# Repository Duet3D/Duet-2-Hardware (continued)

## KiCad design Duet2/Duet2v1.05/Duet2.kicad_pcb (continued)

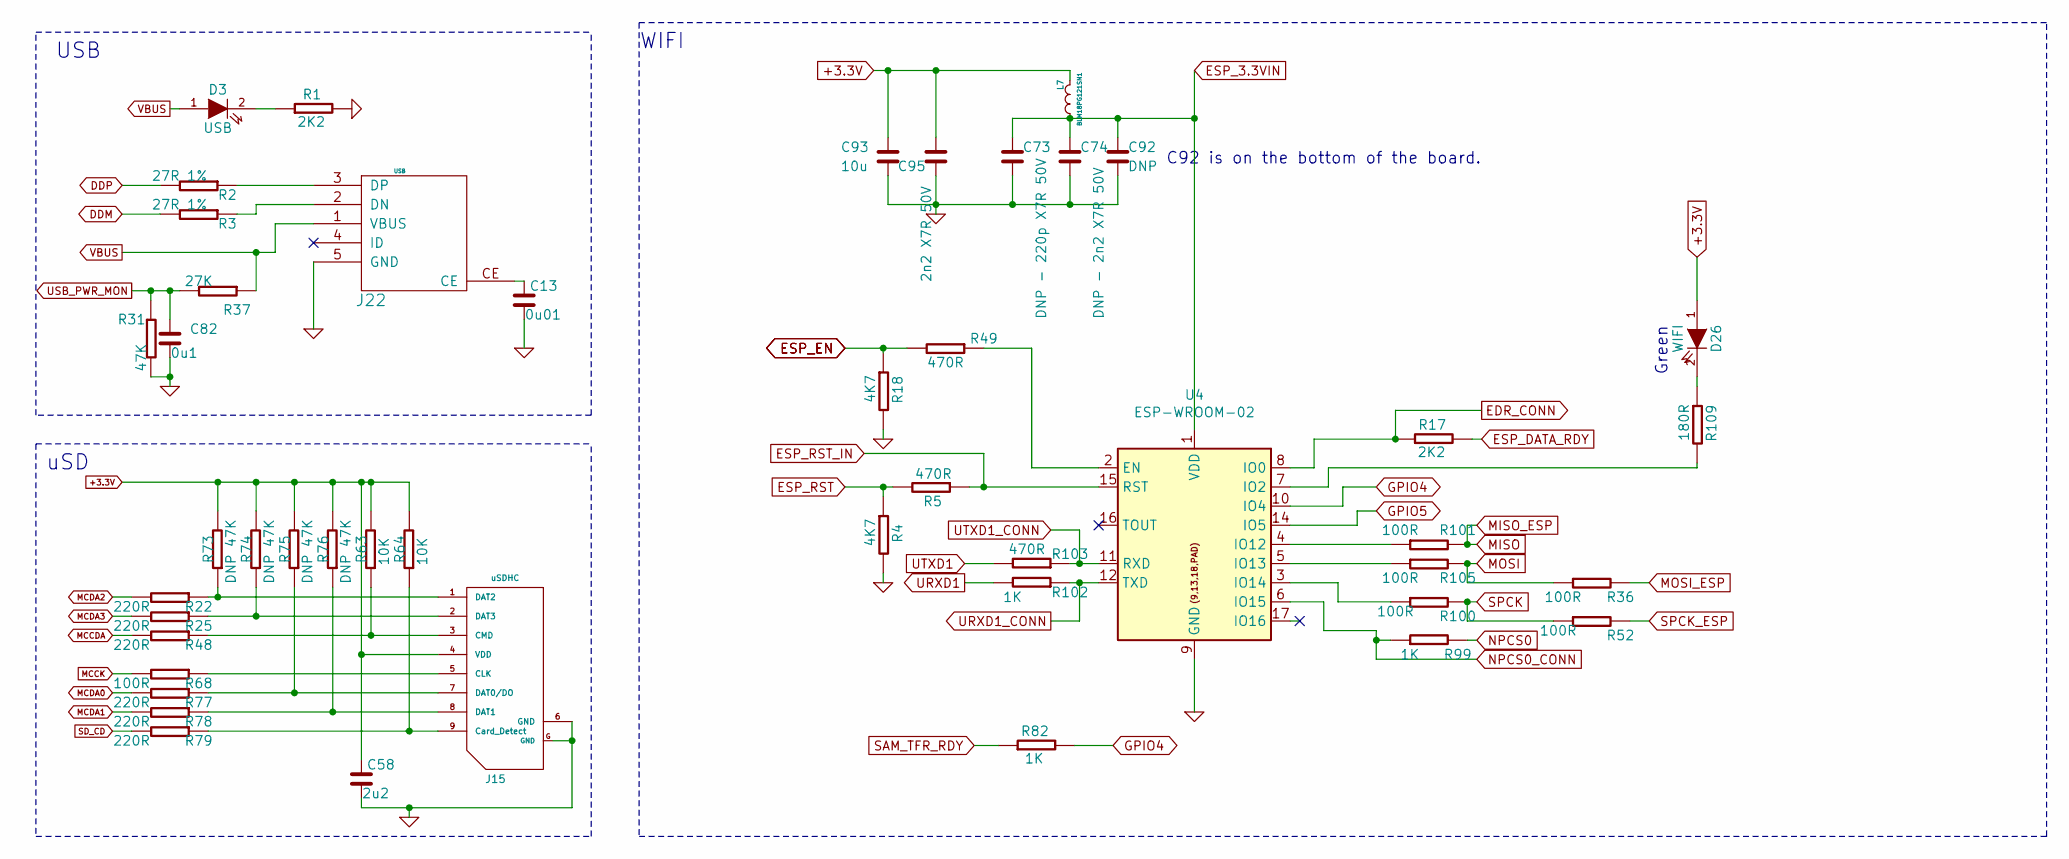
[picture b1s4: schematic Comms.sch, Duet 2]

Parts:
C13: 0u01; C_0603
C58: 2u2; C_0603
C73: DNP - 220p X7R 50V; C_0603
C74: DNP - 2n2 X7R 50V; C_0603
C82: 0u1; C_0603
C92: DNP; C_0603
C93: 10u; C_0805
C95: 2n2 X7R 50V; C_0603
D3: USB; D_0603
D26: WIFI; D_0603
J15: uSDHC; uSD_SKT
J22: USB; uUSB_new
L7: BLM18PG121SN1; L_0603_1608Metric
R1, R17: 2K2; R_0603
R2, R3: 27R 1%; R_0603
R4, R18: 4K7; R_0603
R5, R49, R103: 470R; R_0603
R22, R25, R48, R77, R78, R79: 220R; R_0603
R31: 47K; R_0603
R36, R52, R68, R100, R101, R105: 100R; R_0603
R37: 27K; R_0603
R63, R64: 10K; R_0603
R73, R74, R75, R76: DNP 47K; R_0603
R82, R99, R102: 1K; R_0603
R109: 180R; R_0603
U4: ESP-WROOM-02; Part Number ESP-WROOM-02/U (Internal and External A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

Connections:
+3.3V: C58.1, C93.1, C95.2, D26.1 (A), J15.4 (VDD), L7.1 (A), R63.2, R64.2, R73.2, R74.2, R75.2, R76.2; also elsewhere on the board
DDM: R3.2; also elsewhere on the board
DDP: R2.2; also elsewhere on the board
EDR_CONN: R17.1, U4.8 (IO0); also elsewhere on the board
ESP_3.3VIN: C73.1, C74.1, C92.1, L7.2 (B), U4.1 (VDD); also elsewhere on the board
ESP_DATA_RDY: R17.2; also elsewhere on the board
ESP_EN: R18.1, R49.2; also elsewhere on the board
ESP_RST: R4.1, R5.2; also elsewhere on the board
ESP_RST_IN: R5.1, U4.15 (RST); also elsewhere on the board
GND: C13.2, C58.2, C73.2, C74.2, C82.2, C92.2, C93.2, C95.1, J15.6 (GND), J15.G (GND), J22.5 (GND), R1.2, R4.2, R18.2, R31.2, U4.9 (GND), U4.13 (GND), U4.18 (GND), U4.19 (GND); also elsewhere on the board
GPIO4: R82.2, U4.10 (IO4)
GPIO5: U4.14 (IO5); also elsewhere on the board
MCCDA: R48.2; also elsewhere on the board
MCCK: R68.2; also elsewhere on the board
MCDA0: R77.2; also elsewhere on the board
MCDA1: R78.2; also elsewhere on the board
MCDA2: R22.2; also elsewhere on the board
MCDA3: R25.2; also elsewhere on the board
MISO: R101.2; also elsewhere on the board
MOSI: R36.1, R105.2; also elsewhere on the board
MOSI_ESP: R36.2; also elsewhere on the board
NPCS0: R99.2; also elsewhere on the board
NPCS0_CONN: R99.1, U4.6 (IO15); also elsewhere on the board
unnamed: C13.1, J22.CE
unnamed: D3.2 (K), R1.1
unnamed: D26.2 (K), R109.1
unnamed: J15.1 (DAT2), R22.1, R73.1
unnamed: J15.2 (DAT3), R25.1, R74.1
unnamed: J15.3 (CMD), R48.1, R63.1
unnamed: J15.5 (CLK), R68.1
unnamed: J15.7 (DAT0/DO), R75.1, R77.1
unnamed: J15.8 (DAT1), R76.1, R78.1
unnamed: J15.9 (Card_Detect), R64.1, R79.1
unnamed: J22.2 (DN), R3.1
unnamed: J22.3 (DP), R2.1
unnamed: R49.1, U4.2 (EN)
unnamed: R100.1, U4.3 (IO14)
unnamed: R101.1, U4.4 (IO12)
unnamed: R105.1, U4.5 (IO13)
unnamed: R109.2, U4.7 (IO2)
SAM_TFR_RDY: R82.1; also elsewhere on the board
SD_CD: R79.2; also elsewhere on the board
SPCK: R52.1, R100.2; also elsewhere on the board
SPCK_ESP: R52.2; also elsewhere on the board
URXD1: R102.2; also elsewhere on the board
URXD1_CONN: R102.1, U4.12 (TXD); also elsewhere on the board
USB_PWR_MON: C82.1, R31.1, R37.2; also elsewhere on the board
UTXD1: R103.2; also elsewhere on the board
UTXD1_CONN: R103.1, U4.11 (RXD); also elsewhere on the board
VBUS: D3.1 (A), J22.1 (VBUS), R37.1; also elsewhere on the board

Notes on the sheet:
uSD
WIFI
USB
C92 is on the bottom of the board.
Green

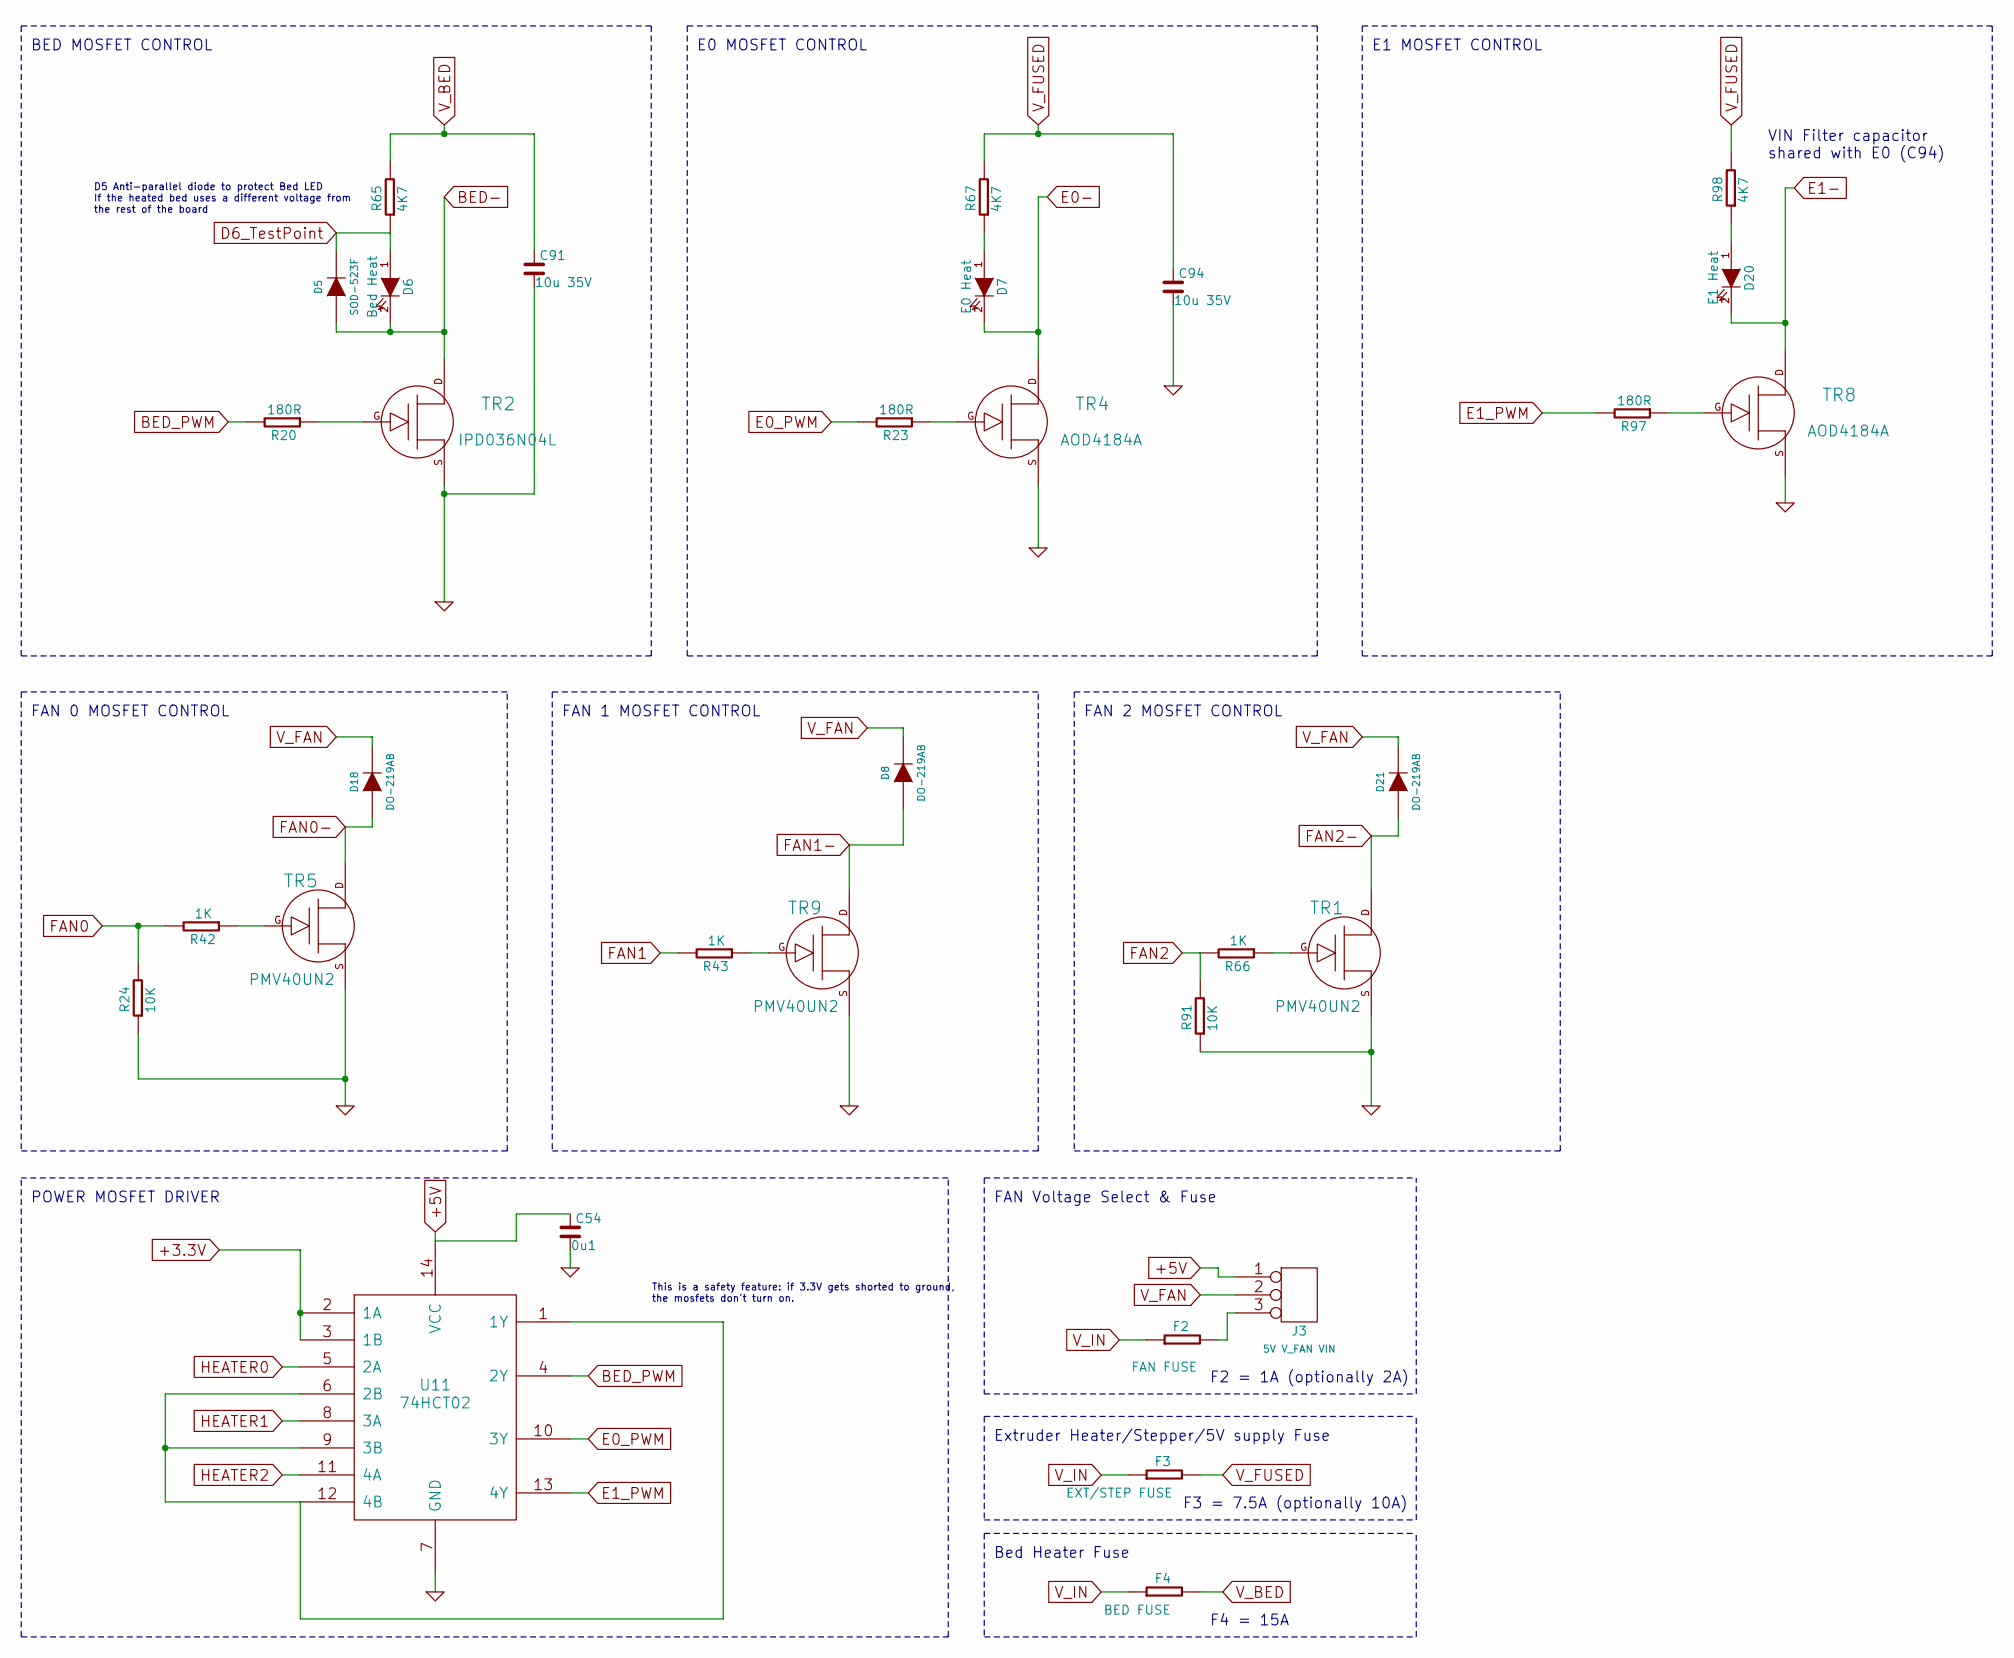
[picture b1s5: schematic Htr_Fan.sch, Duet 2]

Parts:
C54: 0u1; C_0603
C91, C94: 10u 35V; C_1206
D5: SOD-523F
D6: Bed Heat; D_0603
D7: E0 Heat; D_0603
D8, D18, D21: DO-219AB
D20: E1 Heat; D_0603
F2: FAN FUSE; MCCQ-122-minibladefuseholder
F3: EXT/STEP FUSE; MCCQ-122-minibladefuseholder
F4: BED FUSE; MCCQ-122-minibladefuseholder
J3: 5V V_FAN VIN; CONN_3x1
R20, R23, R97: 180R; R_0603
R24, R91: 10K; R_0603
R42, R43, R66: 1K; R_0603
R65, R67, R98: 4K7; R_0603
TR1, TR5, TR9: PMV40UN2; SOT-23
TR2: IPD036N04L; D-PAK
TR4, TR8: AOD4184A; D-PAK
U11: 74HCT02; TSSOP-14

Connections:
+3.3V: U11.2 (1A), U11.3 (1B); also elsewhere on the board
+5V: C54.1, J3.1, U11.14 (VCC); also elsewhere on the board
BED-: D5.2 (A), D6.2 (K), TR2.D; also elsewhere on the board
BED_PWM: R20.2, U11.4 (2Y); also elsewhere on the board
D6_TestPoint: D5.1 (K), D6.1 (A), R65.1; also elsewhere on the board
E0-: D7.2 (K), TR4.D; also elsewhere on the board
E0_PWM: R23.2, U11.10 (3Y); also elsewhere on the board
E1-: D20.2 (K), TR8.D; also elsewhere on the board
E1_PWM: R97.2, U11.13 (4Y); also elsewhere on the board
FAN0: R24.2, R42.2; also elsewhere on the board
FAN0-: D18.2 (A), TR5.D; also elsewhere on the board
FAN1: R43.2; also elsewhere on the board
FAN1-: D8.2 (A), TR9.D; also elsewhere on the board
FAN2: R66.2, R91.2; also elsewhere on the board
FAN2-: D21.2 (A), TR1.D; also elsewhere on the board
GND: C54.2, C91.2, C94.2, R24.1, R91.1, TR1.S, TR2.S, TR4.S, TR5.S, TR8.S, TR9.S, U11.7 (GND); also elsewhere on the board
HEATER0: U11.5 (2A); also elsewhere on the board
HEATER1: U11.8 (3A); also elsewhere on the board
HEATER2: U11.11 (4A); also elsewhere on the board
unnamed: D7.1 (A), R67.1
unnamed: D20.1 (A), R98.1
unnamed: F2.2, J3.3
unnamed: R20.1, TR2.G
unnamed: R23.1, TR4.G
unnamed: R42.1, TR5.G
unnamed: R43.1, TR9.G
unnamed: R66.1, TR1.G
unnamed: R97.1, TR8.G
unnamed: U11.1 (1Y), U11.6 (2B), U11.9 (3B), U11.12 (4B)
V_BED: C91.1, F4.2, R65.2; also elsewhere on the board
V_FAN: D8.1 (K), D18.1 (K), D21.1 (K), J3.2 (PM); also elsewhere on the board
V_FUSED: C94.1, F3.2, R67.2, R98.2; also elsewhere on the board
V_IN: F2.1, F3.1, F4.1; also elsewhere on the board

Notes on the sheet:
FAN 0 MOSFET CONTROL
E0 MOSFET CONTROL
BED MOSFET CONTROL
E1 MOSFET CONTROL
FAN 1 MOSFET CONTROL
POWER MOSFET DRIVER
This is a safety feature: if 3.3V gets shorted to ground, the mosfets don't turn on.
FAN 2 MOSFET CONTROL
D5 Anti-parallel diode to protect Bed LED If the heated bed uses a different voltage from the rest of the board
FAN Voltage Select & Fuse
VIN Filter capacitor shared with E0 (C94)
Extruder Heater/Stepper/5V supply Fuse
Bed Heater Fuse
F2 = 1A (optionally 2A)
F3 = 7.5A (optionally 10A)
F4 = 15A

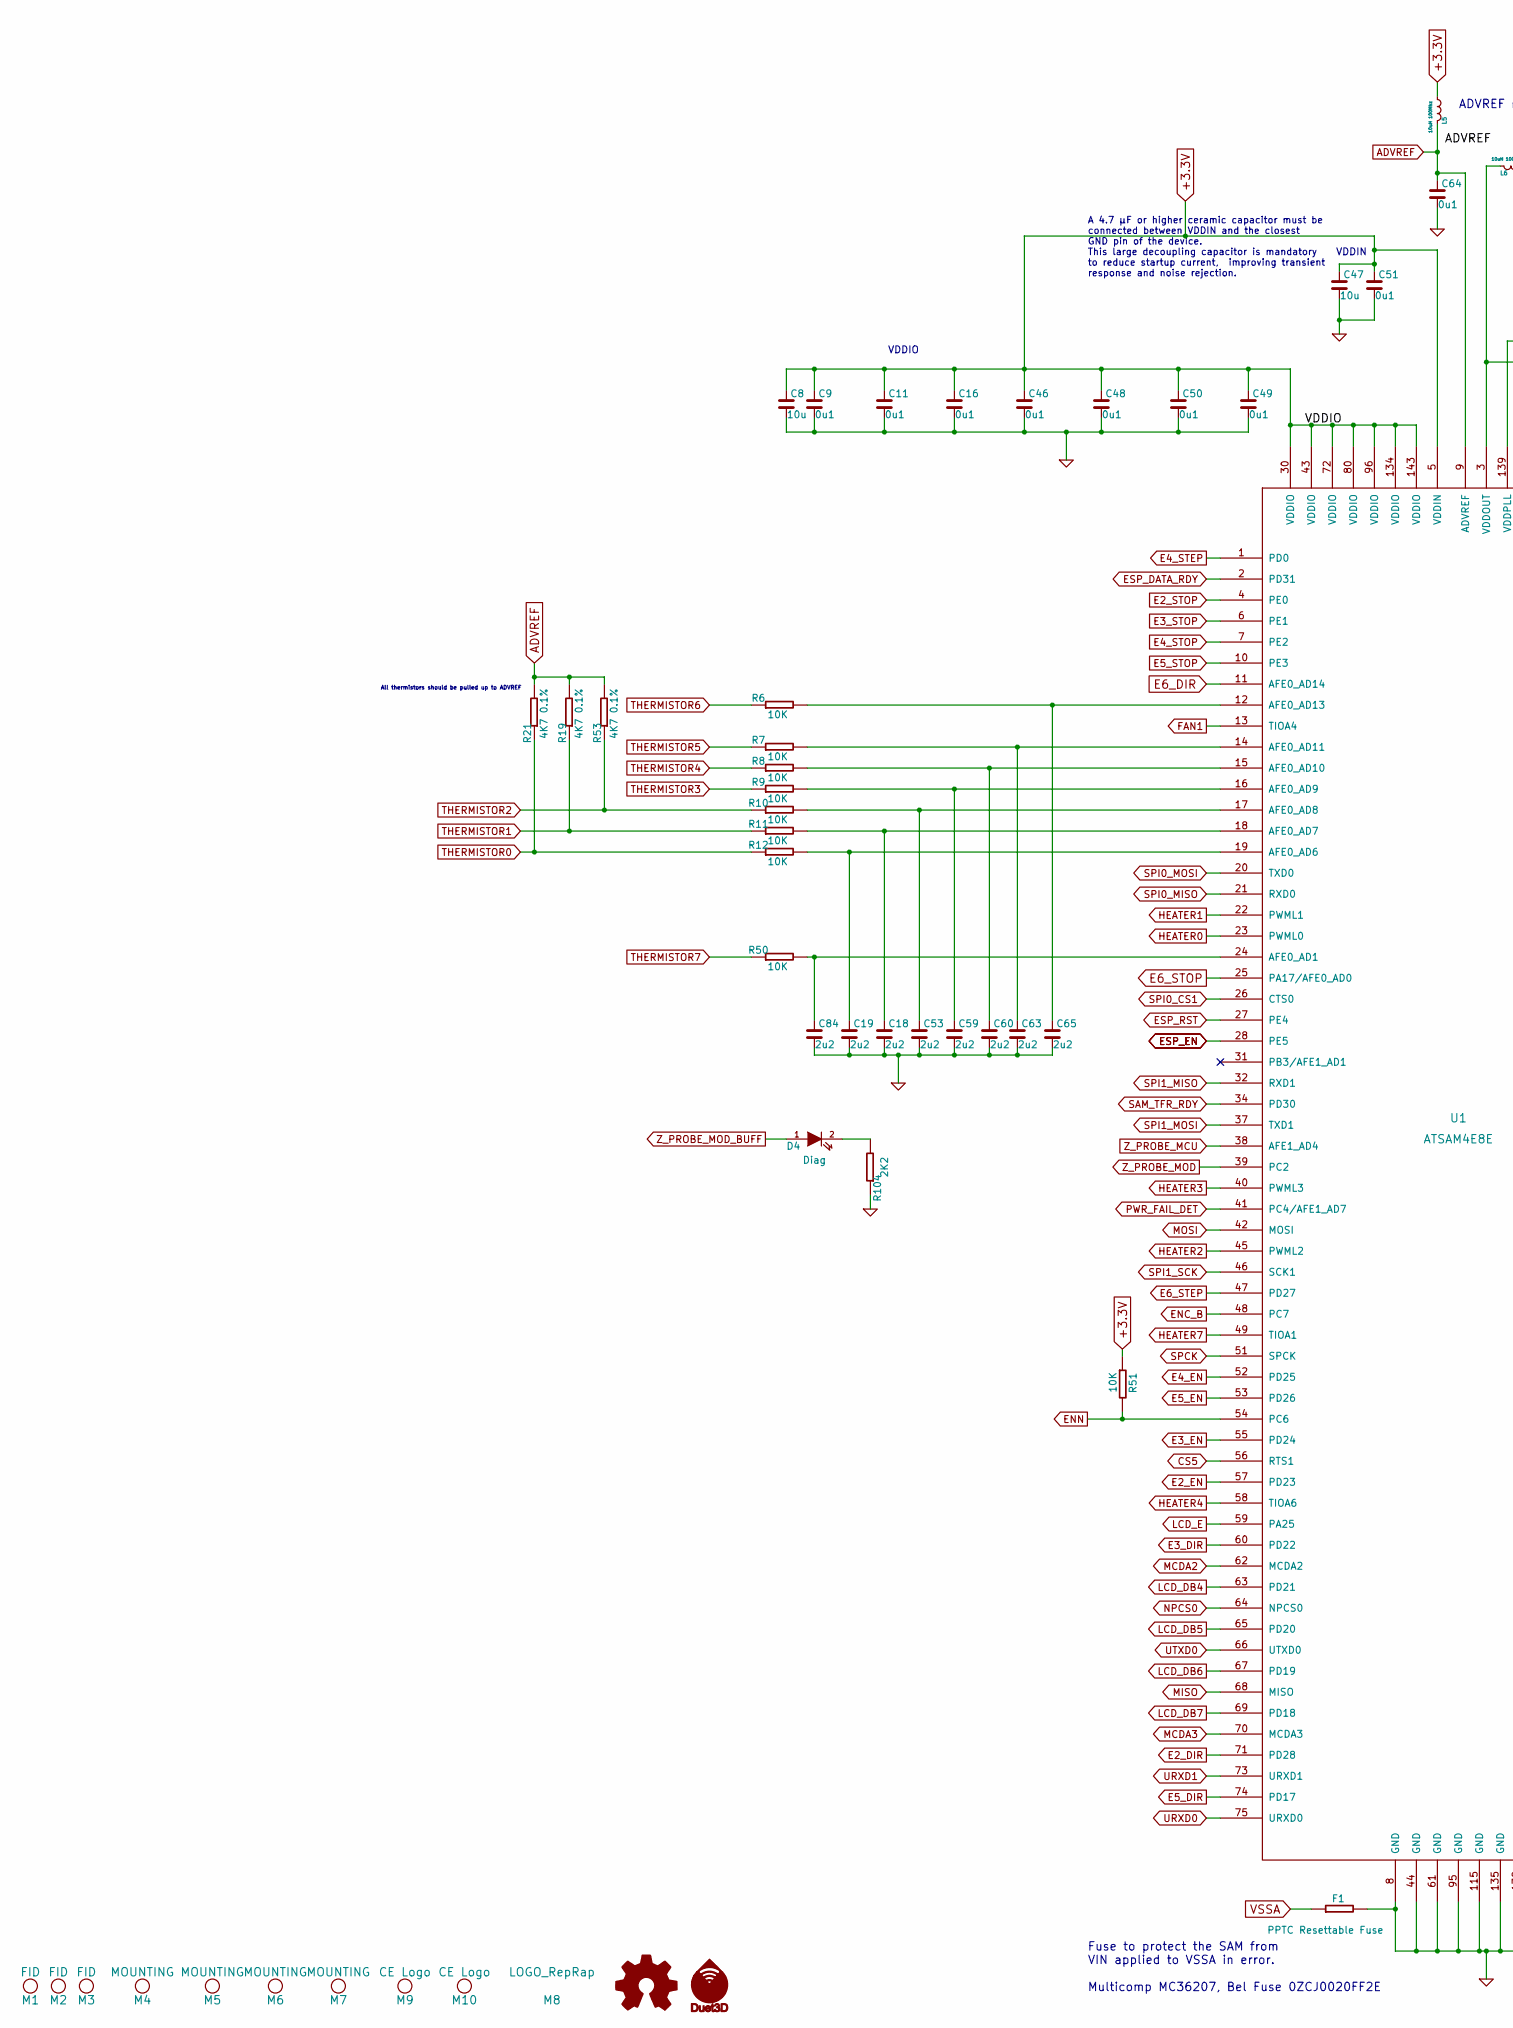
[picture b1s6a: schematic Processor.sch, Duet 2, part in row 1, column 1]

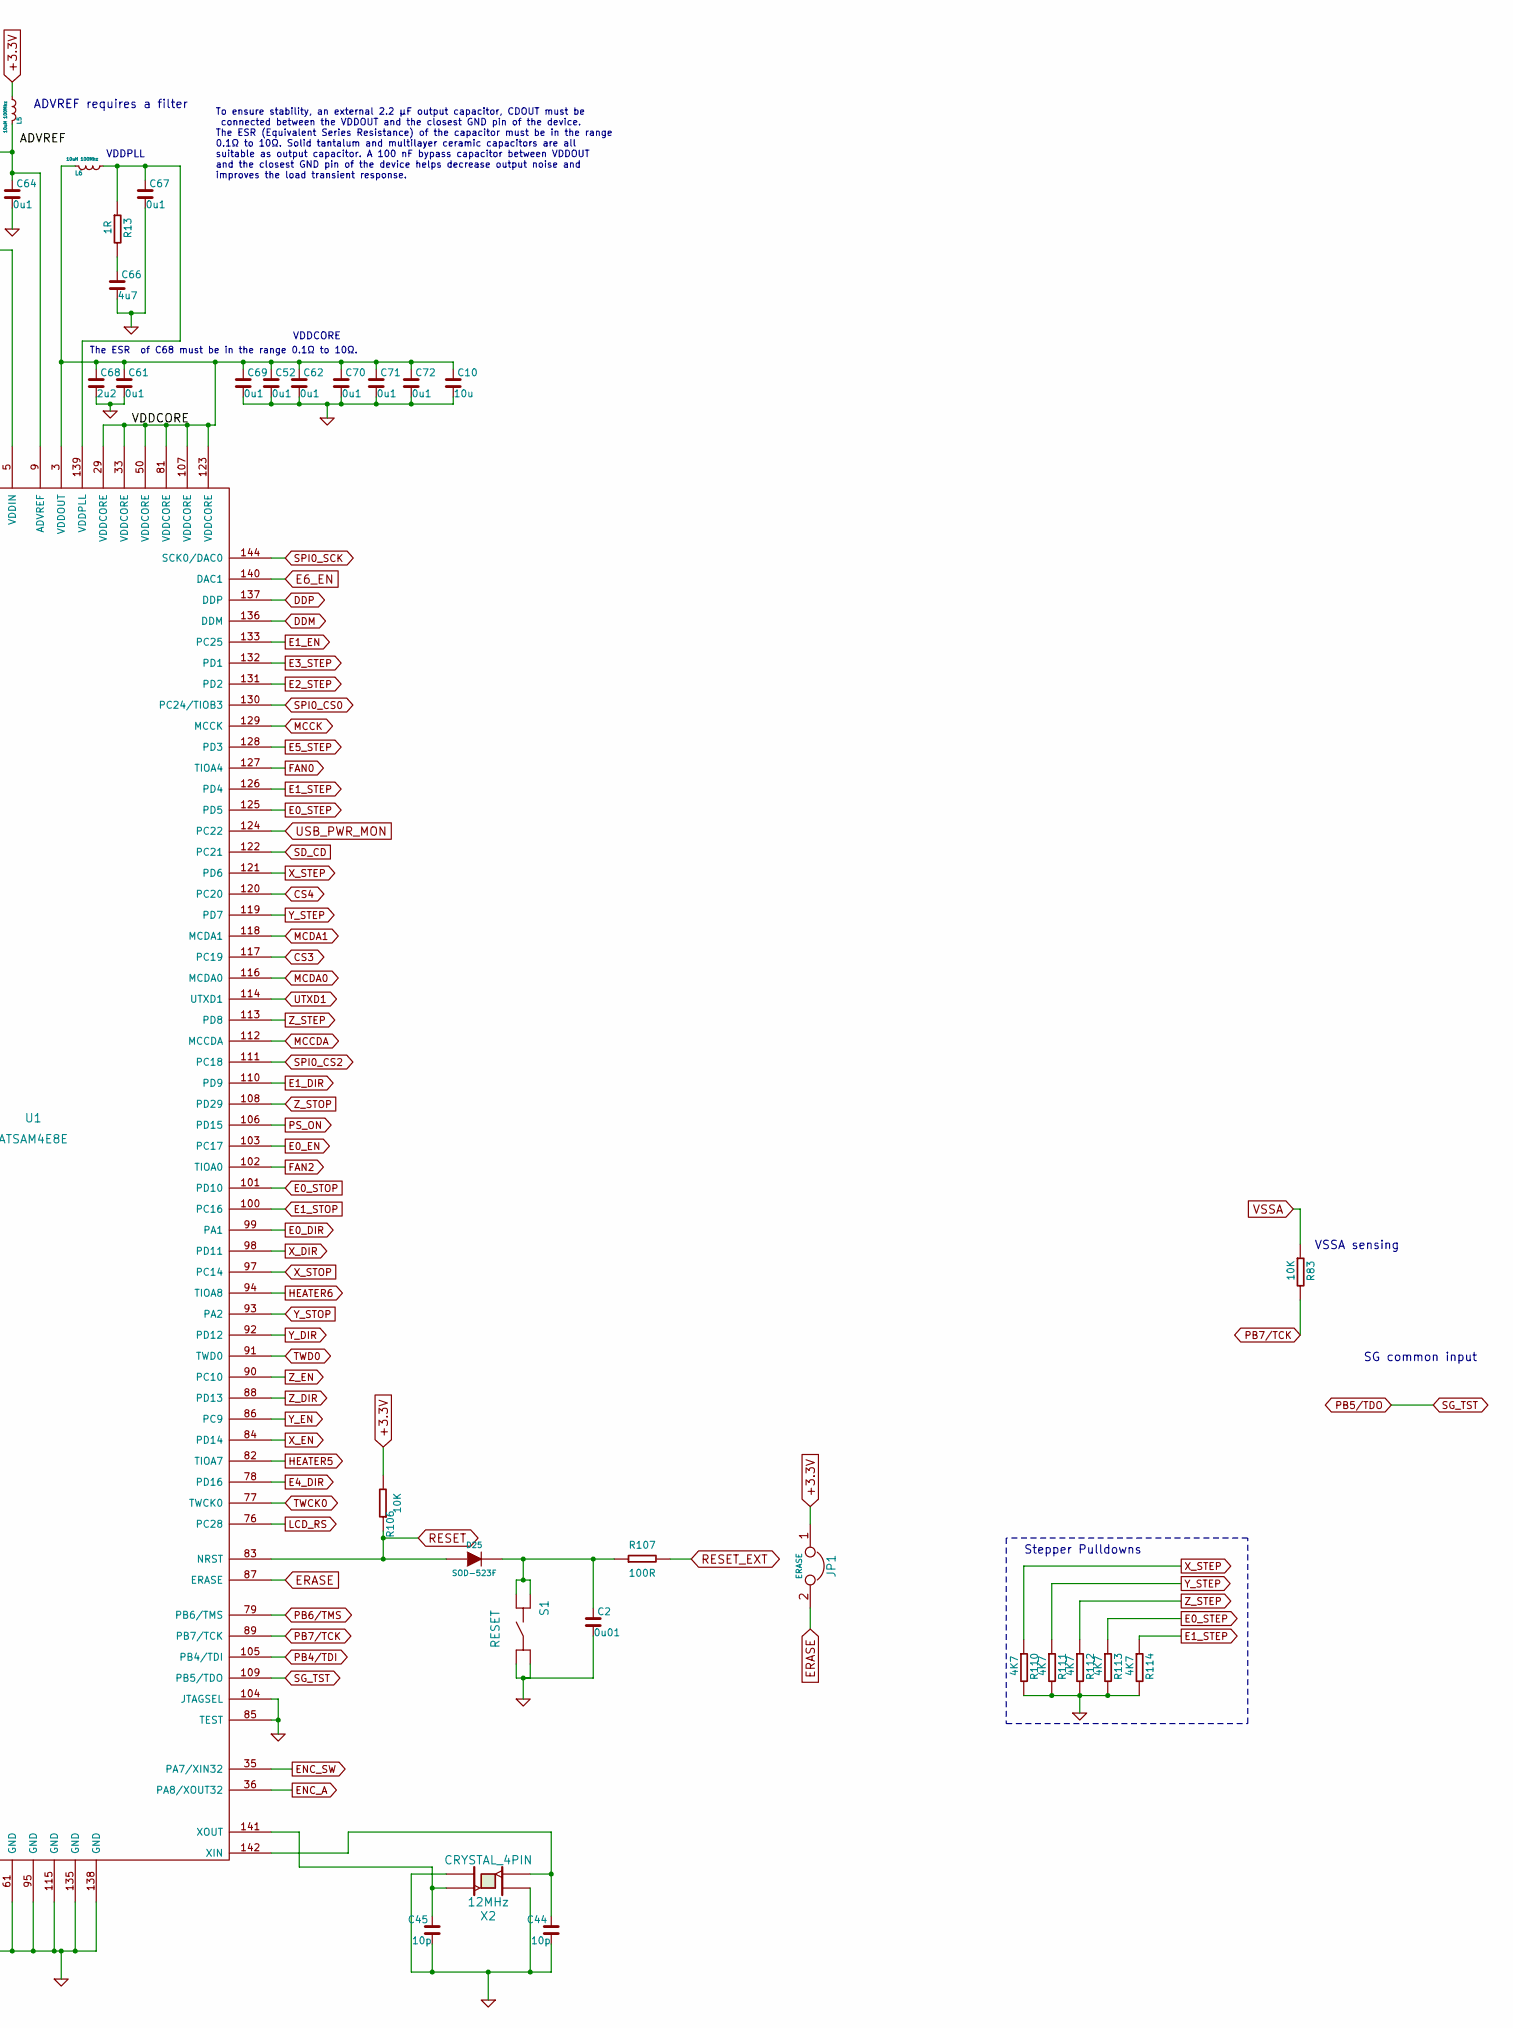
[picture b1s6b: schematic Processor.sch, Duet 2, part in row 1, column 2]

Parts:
C2: 0u01; C_0603
C8, C10, C47: 10u; C_0805
C9, C11, C16, C46, C48, C49, C50, C51, C52, C61, C62, C64, C67, C69, C70, C71, C72: 0u1; C_0603
C18, C19, C53, C59, C60, C63, C65, C68, C84: 2u2; C_0603
C44, C45: 10p; C_0603
C66: 4u7; C_0805
D4: Diag; D_0603
D25: SOD-523F
F1: PPTC Resettable Fuse; R_1206
JP1: ERASE; JUMPER
L5, L6: 10uH 100Mhz; R_0603
M1, M2, M3: FID; Fiducial_1mm_Dia_2.54mm_Outer_CopperTop
M4, M5, M6, M7: MOUNTING; Fixing_M4
M8: LOGO_RepRap; Logo_RepRap
M9: CE Logo; Logo_CE_5mm
M10: CE Logo; Logo_CE_5mm_mirror
M11: Logo_Open_Hardware_Small; OSHW-Logo_11.4x12mm_SilkScreen
M12: Duet3D_Logo; Logo_Duet3D_vertical
R6, R7, R8, R9, R10, R11, R12, R50, R51, R83, R106: 10K; R_0603
R13: 1R; R_0603
R19, R21, R53: 4K7 0.1%; R_0603
R104: 2K2; R_0603
R107: 100R; R_0603
R110, R111, R112, R113, R114: 4K7; R_0603
S1: RESET; SW_SIDE_1_lugs
U1: ATSAM4E8E; LQFP144
X2: CRYSTAL_4PIN; Xtal_5x3.2

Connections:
+3.3V: C8.1, C9.1, C11.1, C16.1, C46.1, C47.1, C48.1, C49.1, C50.1, C51.1, JP1.1, L5.2 (B), R51.1, R106.2, U1.5 (VDDIN), U1.30 (VDDIO), U1.43 (VDDIO), U1.72 (VDDIO), U1.80 (VDDIO), U1.96 (VDDIO), U1.134 (VDDIO), U1.143 (VDDIO); also elsewhere on the board
/Processor/VDDCORE: C10.1, C52.1, C61.1, C62.1, C68.1, C69.1, C70.1, C71.1, C72.1, L6.1 (A), U1.3 (VDDOUT), U1.29 (VDDCORE), U1.33 (VDDCORE), U1.50 (VDDCORE), U1.81 (VDDCORE), U1.107 (VDDCORE), U1.123 (VDDCORE)
ADVREF: C64.1, L5.1 (A), R19.2, R21.2, R53.2, U1.9 (ADVREF); also elsewhere on the board
CS3: U1.117 (PC19); also elsewhere on the board
CS4: U1.120 (PC20); also elsewhere on the board
CS5: U1.56 (RTS1); also elsewhere on the board
DDM: U1.136 (DDM); also elsewhere on the board
DDP: U1.137 (DDP); also elsewhere on the board
E0_DIR: U1.99 (PA1); also elsewhere on the board
E0_EN: U1.103 (PC17); also elsewhere on the board
E0_STEP: R113.1, U1.125 (PD5); also elsewhere on the board
E0_STOP: U1.101 (PD10); also elsewhere on the board
E1_DIR: U1.110 (PD9); also elsewhere on the board
E1_EN: U1.133 (PC25); also elsewhere on the board
E1_STEP: R114.1, U1.126 (PD4); also elsewhere on the board
E1_STOP: U1.100 (PC16); also elsewhere on the board
E2_DIR: U1.71 (PD28); also elsewhere on the board
E2_EN: U1.57 (PD23); also elsewhere on the board
E2_STEP: U1.131 (PD2); also elsewhere on the board
E2_STOP: U1.4 (PE0); also elsewhere on the board
E3_DIR: U1.60 (PD22); also elsewhere on the board
E3_EN: U1.55 (PD24); also elsewhere on the board
E3_STEP: U1.132 (PD1); also elsewhere on the board
E3_STOP: U1.6 (PE1); also elsewhere on the board
E4_DIR: U1.78 (PD16); also elsewhere on the board
E4_EN: U1.52 (PD25); also elsewhere on the board
E4_STEP: U1.1 (PD0); also elsewhere on the board
E4_STOP: U1.7 (PE2); also elsewhere on the board
E5_DIR: U1.74 (PD17); also elsewhere on the board
E5_EN: U1.53 (PD26); also elsewhere on the board
E5_STEP: U1.128 (PD3); also elsewhere on the board
E5_STOP: U1.10 (PE3); also elsewhere on the board
E6_DIR: U1.11 (AFE0_AD14); also elsewhere on the board
E6_EN: U1.140 (DAC1); also elsewhere on the board
E6_STEP: U1.47 (PD27); also elsewhere on the board
E6_STOP: U1.25 (PA17/AFE0_AD0); also elsewhere on the board
ENC_A: U1.36 (PA8/XOUT32); also elsewhere on the board
ENC_B: U1.48 (PC7); also elsewhere on the board
ENC_SW: U1.35 (PA7/XIN32); also elsewhere on the board
ENN: R51.2, U1.54 (PC6); also elsewhere on the board
ERASE: JP1.2, U1.87 (ERASE)
ESP_DATA_RDY: U1.2 (PD31); also elsewhere on the board
ESP_EN: U1.28 (PE5); also elsewhere on the board
ESP_RST: U1.27 (PE4); also elsewhere on the board
FAN0: U1.127 (TIOA4); also elsewhere on the board
FAN1: U1.13 (TIOA4); also elsewhere on the board
FAN2: U1.102 (TIOA0); also elsewhere on the board
GND: C2.2, C8.2, C9.2, C10.2, C11.2, C16.2, C18.2, C19.2, C44.2, C45.2, C46.2, C47.2, C48.2, C49.2, C50.2, C51.2, C52.2, C53.2, C59.2, C60.2, C61.2, C62.2, C63.2, C64.2, C65.2, C66.2, C67.2, C68.2, C69.2, C70.2, C71.2, C72.2, C84.2, F1.2, R104.1, R110.2, R111.2, R112.2, R113.2, R114.2, S1.1, S1.2, U1.8 (GND), U1.44 (GND), U1.61 (GND), U1.85 (TEST), U1.95 (GND), U1.104 (JTAGSEL), U1.115 (GND), U1.135 (GND), U1.138 (GND), X2.2, X2.4; also elsewhere on the board
HEATER0: U1.23 (PWML0); also elsewhere on the board
HEATER1: U1.22 (PWML1); also elsewhere on the board
HEATER2: U1.45 (PWML2); also elsewhere on the board
HEATER3: U1.40 (PWML3); also elsewhere on the board
HEATER4: U1.58 (TIOA6); also elsewhere on the board
HEATER5: U1.82 (TIOA7); also elsewhere on the board
HEATER6: U1.94 (TIOA8); also elsewhere on the board
HEATER7: U1.49 (TIOA1); also elsewhere on the board
LCD_DB4: U1.63 (PD21); also elsewhere on the board
LCD_DB5: U1.65 (PD20); also elsewhere on the board
LCD_DB6: U1.67 (PD19); also elsewhere on the board
LCD_DB7: U1.69 (PD18); also elsewhere on the board
LCD_E: U1.59 (PA25); also elsewhere on the board
LCD_RS: U1.76 (PC28); also elsewhere on the board
MCCDA: U1.112 (MCCDA); also elsewhere on the board
MCCK: U1.129 (MCCK); also elsewhere on the board
MCDA0: U1.116 (MCDA0); also elsewhere on the board
MCDA1: U1.118 (MCDA1); also elsewhere on the board
MCDA2: U1.62 (MCDA2); also elsewhere on the board
MCDA3: U1.70 (MCDA3); also elsewhere on the board
MISO: U1.68 (MISO); also elsewhere on the board
MOSI: U1.42 (MOSI); also elsewhere on the board
NPCS0: U1.64 (NPCS0); also elsewhere on the board
unnamed: C2.1, D25.1 (K), R107.1, S1.3, S1.4
unnamed: C18.1, R11.2, U1.18 (AFE0_AD7)
unnamed: C19.1, R12.2, U1.19 (AFE0_AD6)
unnamed: C44.1, U1.142 (XIN), X2.3
unnamed: C45.1, U1.141 (XOUT), X2.1
unnamed: C53.1, R10.2, U1.17 (AFE0_AD8)
unnamed: C59.1, R9.2, U1.16 (AFE0_AD9)
unnamed: C60.1, R8.2, U1.15 (AFE0_AD10)
unnamed: C63.1, R7.2, U1.14 (AFE0_AD11)
unnamed: C65.1, R6.2, U1.12 (AFE0_AD13)
unnamed: C66.1, R13.2
unnamed: C67.1, L6.2 (B), R13.1, U1.139 (VDDPLL)
unnamed: C84.1, R50.2, U1.24 (AFE0_AD1)
unnamed: D4.2 (K), R104.2
PB4/TDI: U1.105 (PB4/TDI)
PB5/TDO: U1.109 (PB5/TDO); also elsewhere on the board
PB6/TMS: U1.79 (PB6/TMS); also elsewhere on the board
PB7/TCK: R83.2, U1.89 (PB7/TCK)
PS_ON: U1.106 (PD15); also elsewhere on the board
PWR_FAIL_DET: U1.41 (PC4/AFE1_AD7); also elsewhere on the board
RESET: D25.2 (A), R106.1, U1.83 (NRST)
RESET_EXT: R107.2; also elsewhere on the board
SAM_TFR_RDY: U1.34 (PD30); also elsewhere on the board
SD_CD: U1.122 (PC21); also elsewhere on the board
SPCK: U1.51 (SPCK); also elsewhere on the board
SPI0_CS0: U1.130 (PC24/TIOB3); also elsewhere on the board
SPI0_CS1: U1.26 (CTS0); also elsewhere on the board
SPI0_CS2: U1.111 (PC18); also elsewhere on the board
SPI0_MISO: U1.21 (RXD0); also elsewhere on the board
SPI0_MOSI: U1.20 (TXD0); also elsewhere on the board
SPI0_SCK: U1.144 (SCK0/DAC0); also elsewhere on the board
SPI1_MISO: U1.32 (RXD1); also elsewhere on the board
SPI1_MOSI: U1.37 (TXD1); also elsewhere on the board
SPI1_SCK: U1.46 (SCK1); also elsewhere on the board
THERMISTOR0: R12.1, R21.1; also elsewhere on the board
THERMISTOR1: R11.1, R19.1; also elsewhere on the board
THERMISTOR2: R10.1, R53.1; also elsewhere on the board
THERMISTOR3: R9.1; also elsewhere on the board
THERMISTOR4: R8.1; also elsewhere on the board
THERMISTOR5: R7.1; also elsewhere on the board
THERMISTOR6: R6.1; also elsewhere on the board
THERMISTOR7: R50.1; also elsewhere on the board
TWCK0: U1.77 (TWCK0); also elsewhere on the board
TWD0: U1.91 (TWD0); also elsewhere on the board
URXD0: U1.75 (URXD0); also elsewhere on the board
URXD1: U1.73 (URXD1); also elsewhere on the board
USB_PWR_MON: U1.124 (PC22); also elsewhere on the board
UTXD0: U1.66 (UTXD0); also elsewhere on the board
UTXD1: U1.114 (UTXD1); also elsewhere on the board
VSSA: F1.1, R83.1; also elsewhere on the board
X_DIR: U1.98 (PD11); also elsewhere on the board
X_EN: U1.84 (PD14); also elsewhere on the board
X_STEP: R110.1, U1.121 (PD6); also elsewhere on the board
X_STOP: U1.97 (PC14); also elsewhere on the board
Y_DIR: U1.92 (PD12); also elsewhere on the board
Y_EN: U1.86 (PC9); also elsewhere on the board
Y_STEP: R111.1, U1.119 (PD7); also elsewhere on the board
Y_STOP: U1.93 (PA2); also elsewhere on the board
Z_DIR: U1.88 (PD13); also elsewhere on the board
Z_EN: U1.90 (PC10); also elsewhere on the board
Z_PROBE_MCU: U1.38 (AFE1_AD4); also elsewhere on the board
Z_PROBE_MOD: U1.39 (PC2); also elsewhere on the board
Z_PROBE_MOD_BUFF: D4.1 (A); also elsewhere on the board
Z_STEP: R112.1, U1.113 (PD8); also elsewhere on the board
Z_STOP: U1.108 (PD29); also elsewhere on the board

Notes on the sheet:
VDDPLL
VDDCORE
VDDIO
VDDIN
A 4.7 μF or higher ceramic capacitor must be connected between VDDIN and the closest GND pin of the device. This large decoupling capacitor is mandatory to reduce startup current, improving transient response and noise rejection.
To ensure stability, an external 2.2 μF output capacitor, CDOUT must be connected between the VDDOUT and the closest GND pin of the device. The ESR (Equivalent Series Resistance) of the capacitor must be in the range 0.1Ω to 10Ω. Solid tantalum and multilayer ceramic capacitors are all suitable as 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
Fuse to protect the SAM from VIN applied to VSSA in error. Multicomp MC36207, Bel Fuse 0ZCJ0020FF2E
The ESR of C68 must be in the range 0.1Ω to 10Ω.
All thermistors should be pulled up to ADVREF
ADVREF requires a filter
VSSA sensing
SG common input
Stepper Pulldowns
